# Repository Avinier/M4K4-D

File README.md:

# Makad / M4K4-D

> **Current project overview**: last reconciled **12 November 2026**
>
> Foundation approved: **14 August 2026** · V1 deadline: **5 December 2026**

**Makad**, technical designation **M4K4-D** and commonly shortened to **M4**, is a personal droid. M4 is intended to occupy the kind of companion role R2-D2 occupied for Luke Skywalker: recognizable, attentive, expressive, and full of character.

The central V1 priority is simple:

> **M4 should feel alive.**

Makad's defining advantage is expressiveness. That expression comes from what M4 understands, sees, and hears, and from how convincingly its display, status light, astromech audio, head, wheeled base, and timing communicate one intent.

## Authority

- [`project/00-foundation`](project/00-foundation/) is the product-intent authority.
- [`project/03-build`](project/03-build/README.md) governs every engineering decision, part selection, BOM change and CAD edit from 2026-09-28. Its ledger is [`decisions.md`](project/03-build/decisions.md) and its parts register is [`BOM.csv`](project/03-build/BOM.csv).
- [`project/01-system`](project/01-system/) and [`project/02-prototypes`](project/02-prototypes/) are read-only engineering reference. Where they disagree with `03-build`, `03-build` wins.

[`MEMORY.md`](MEMORY.md) is a short chronological log of the project's turning points.

## Current design

M4 is a battery-powered floor droid with a three-axis head, an animated face, a camera-side status light, body-mounted hearing and speech, and a two-wheel base. The head carries the display, camera, status light and C2 motion controller. The body carries the yaw stage, four I²S microphones, the speaker, main compute and the bought power modules; the chassis carries the battery, drive and floor sensors. Floor mode is primary; tabletop mode inhibits locomotion by default.

Drive geometry is Ø84 mm wheels on a ~170 mm track with a front ball caster and a mandatory rear anti-tip keel ([dimensional baseline](project/01-system/dimensional-baseline.md) v1.15). The whole robot is modelled in [`project/03-build/final/v1`](project/03-build/final/v1/README.md); subsystem CAD lives in [01-chassis](project/03-build/01-chassis/), [02-body](project/03-build/02-body/) and [03-head](project/03-build/03-head/).

### Selected components

States follow the [BOM](project/03-build/BOM.csv): selected parts are settled but not yet measured or bench-proven.

| Item | Selection | Record |
|---|---|---|
| Face display | Waveshare ESP32-S3-LCD-4.3, **no-touch, SKU 30493**: 800×480 IPS with on-board ESP32-S3/LVGL renderer | [display study](project/01-system/display-candidate-study.md) |
| Head camera | Raspberry Pi Camera Module 3 **Wide**, **SC0874**; ribbon crosses pitch and roll in a free loop behind the head | [D-105](project/03-build/decisions.md#d-105) |
| Main compute (C0) | **Raspberry Pi 5, 2 GB** with the official Active Cooler, on PCB-09 (2 × RS-422 link adapter) | [D-048](project/03-build/decisions.md#d-048), [04-pcbs](project/03-build/04-pcbs/README.md) |
| Head motion controller (C2) | Waveshare **ESP32-S3-Zero** on the custom PCB-12 carrier | [D-102](project/03-build/decisions.md#d-102) |
| Base controller (C3) | Espressif **ESP32-S3-DevKitC-1 v1.1** on the custom PCB-10 carrier | [04-pcbs](project/03-build/04-pcbs/README.md) |
| Head actuators | Yaw: **Waveshare ST3215-HS** at 11.1 V. Pitch and roll: **Feetech STS3045M** at 6.3 V. Candidates until bench tests B1–B6 | [D-046](project/03-build/decisions.md#d-046)–[D-049](project/03-build/decisions.md#d-049) |
| Drive | **ThinkRobotics MOT3001-6V230RPM** encoder gearmotors (received), two DRV8833 carriers, printed PETG/TPU wheels, Pololu #2691 ball caster | [D-003](project/03-build/decisions.md#d-003) |
| Battery | **2S1P Samsung INR18650-25R** (7.2 V, 18 Wh) with a bought TIFPS0629 protection board and copper ballast; charged off-board (ISDT PD60) | [D-093](project/03-build/decisions.md#d-093) |
| Power | Pololu #2813 pushbutton switch, two S18V20ALV servo rails, two S13V30F5 5 V rails, INA226 monitor | [D-094](project/03-build/decisions.md#d-094), [module selection](project/03-build/module-selection.md) |
| Audio and IMU | Visaton K 50 WP speaker, MAX98357A amp, 4 × INMP441 mics, Adafruit LSM6DSOX base IMU | [D-094](project/03-build/decisions.md#d-094) |
| Control split | C0 owns semantic behaviour; D1 renders eyes; C2 owns head trajectory and local safety; C3 owns base loops and local hazards. Links are differential UART; C2 relays face/light state locally | [control topology](project/01-system/control-topology-options.md) |

## Current build state

The design is ahead of the physical robot. The whole-robot CAD is integrated and checked; first parts have arrived; nothing is printed, wired or running.

| Area | State (2026-11-12) |
|---|---|
| CAD | Chassis, body and head v1 are integrated in `final/v1` with targeted checks. Tipping margin a_tip 1.670 neutral / 1.646 worst pose against 1.582 ([D-095](project/03-build/decisions.md#d-095)); camera-loop ballast keeps the worst-yaw margin above 1.5% ([D-105](project/03-build/decisions.md#d-105)). Not yet a fabrication release for body and head. |
| Electrical | D-093 replaced the custom power boards with bought modules. The [harness](project/03-build/05-harness/README.md) topology is drawn but on **electrical HOLD** ([D-096](project/03-build/decisions.md#d-096)). Custom boards: PCB-09 rev B routed; PCB-10/11/15 rev A; PCB-08/12/14/16 rev A drafts, not ordered. |
| Procurement | Modules and small parts ordered 2026-11-08; deliveries logged in [BOM-deliveries.md](project/03-build/BOM-deliveries.md). Open actions in [TODO.md](project/03-build/TODO.md). |
| Printing | Chassis print package exported to [04-print](project/04-print/README.md); body and head prints not started. |
| Software / firmware | [Firmware requirements](project/03-build/04-software/firmware-requirements.md) recorded; timebase, link contract and behaviour are specified more than implemented. |
| Physical tests | None run. Bench register N1–N12 and actuator tests B1–B6 are open. |

`visuals/` are provisional references; several show superseded details (mouths, ear microphones, yoke-mounted ears).

## Immediate next work

- **Receive and measure** the ordered parts; record them in the BOM and correct dependent CAD.
- **Run the bench tests**: power switch, servo and 5 V rails (N1–N12), Feetech actuators (B1–B6), pack protection acceptance.
- **Clear the harness HOLD** from measured peaks, then build and test the harness.
- **Finish the custom boards** (PCB-08, 12, 14, 16) and order all of them together.
- **Print and assemble the chassis**, then body and head, through [04-print](project/04-print/README.md).
- **Implement firmware and software** on the same timeline: C2/C3, C0 behaviour and perception, the serial link and face rendering.

## Documents

### Product intent: authoritative

- [Vision](project/00-foundation/vision.md)
- [V1 scope](project/00-foundation/v1-scope.md)
- [Constraints](project/00-foundation/constraints.md)
- [Success criteria](project/00-foundation/success-criteria.md)
- [Core interaction scenarios](project/00-foundation/core-interaction-scenarios.md)

### Build: governing

- [03-build overview](project/03-build/README.md): status, file map and build rules
- [Decisions ledger](project/03-build/decisions.md), [BOM](project/03-build/BOM.csv), [simplification plan](project/03-build/simplification-plan.md)
- [Whole robot (final v1)](project/03-build/final/v1/README.md) and its [print guide](project/03-build/final/v1/printguide.md)
- [Custom PCBs](project/03-build/04-pcbs/README.md), [harness](project/03-build/05-harness/README.md)
- [Printing](project/04-print/README.md)

### Engineering reference (read-only)

- [Dimensional and packaging baseline](project/01-system/dimensional-baseline.md)
- Ledgers: [mass/envelope](project/01-system/mass-envelope-ledger.md), [power/energy/thermal](project/01-system/power-energy-ledger.md), [candidate sourcing](project/01-system/candidate-sourcing-matrix.md)
- Studies: [control topology](project/01-system/control-topology-options.md), [display](project/01-system/display-candidate-study.md), [camera](project/01-system/camera-candidate-study.md), [head harness](project/01-system/head-harness-routing-study.md), [timebase](project/01-system/timebase.md)
- [System design brief](project/01-system/system-design-brief.md), [risk-prototype plan](project/01-system/risk-prototype-plan.md), [workbench](project/01-system/workbench.md), [run-record convention](project/01-system/run-record-convention.md)
- Risk prototypes: [head](project/02-prototypes/RP-01-head/), [electrical](project/02-prototypes/RP-02-electrical/README.md), [locomotion](project/02-prototypes/RP-03-locomotion/README.md), [coordination](project/02-prototypes/RP-04-coordination/README.md), [interaction](project/02-prototypes/RP-05-interaction/README.md), [CAD layouts](project/02-prototypes/RP-06-cad/README.md), [following](project/02-prototypes/RP-07-following/README.md)
- Earlier memory logs: [`archive/`](archive/)

## Repository

```
project/00-foundation/   product intent and constraints      authoritative
project/01-system/       system studies and ledgers          reference
project/02-prototypes/   risk prototypes and early CAD       reference
project/03-build/        decisions, BOM, CAD, PCBs, harness  governs
project/04-print/        print lab, workflow, STL exports
visuals/                 provisional renders
archive/                 earlier memory logs
MEMORY.md                chronological log of turning points
README.md                this orientation
```

## Identity and design direction

M4 is a droid, not a desktop assistant, smart speaker, or generic social robot. The approved direction is:

- strongly inspired by Star Wars droids;
- cyberpunk, rugged, scrappy, and characterful;
- mechanical rather than glossy or appliance-like;
- modular and screw-together, with visible fasteners, panels, seams, and service access as part of the personality;
- eyes only on the face, no mouth;
- approachable without optimizing for minimum size;
- open to substantial redesign from the current renders.

## V1 Core

V1 is not complete unless the following outcomes work together as one droid. Exact wording lives in [`v1-scope.md`](project/00-foundation/v1-scope.md) (SCOPE-01…21).

**Expression and character** — animated face on the onboard display; powered roll, pitch and yaw head motion; at least one controllable LED beside the camera; a builder-authored non-English astromech language; idle aliveness without manual control; display, LED, audio, head, base and timing express one intent; at least one bounded excited spin.

**Understanding and perception** — natural spoken interaction within the approved scenarios; invocation forms **"M4," "M4K4," and "Makad"**; visual acquisition of a nearby person or face; tracking maintained or reacquired through later-defined test cases.

**Mobility and following** — battery-powered wheeled floor droid; "come here" finds, approaches and stops at a bounded distance; "follow me" tracks the selected person through an approved indoor route; obstacles, stopping, target loss and unsafe conditions are handled without continuing blindly.

**Utility and entertainment** — display the time; create and signal timers and alarms; start Spotify playback through an approved integration; eyes "vibe" to music.

**Operation and construction** — untethered on onboard battery for at least 20 minutes; floor mode primary; tabletop mode inhibits locomotion by default and protects edges; accessible stop or cutoff with bounded failure; assembled, started, demonstrated, inspected and serviced from documentation.

**Candidate:** spatial/directional hearing, included only if it materially improves an approved interaction. Everything else is uncommitted; there is no permanent "never" list.

## Approved Core scenarios

Source: [`core-interaction-scenarios.md`](project/00-foundation/core-interaction-scenarios.md).

**1. Wake, socialize, assist.** M4 idles head-down. A person calls its name. M4 wakes as one coordinated performance: three-axis head rise, eyes, camera-side LED, astromech acknowledgement, face acquisition and gaze. A greeting produces an in-character response. The person can request the time, a timer, an alarm, or Spotify playback; M4 confirms visibly, performs it, and vibes during music.

**2. Come here and follow me.** On an approved floor, the person invokes M4 and says "come here." M4 acknowledges, searches, acquires, turns, approaches safely and stops approximately 0.6–0.9 m away. "Follow me" makes M4 follow through an approved route of up to about 3 m at no more than about 0.5 m/s while handling obstacles and target loss. When continuing is unsafe, M4 stops and says so. M4 performs an excited spin and settles.

## Success definition

V1 succeeds when M4 delivers these interactions as a convincing, repeatable droid encounter on battery power, not as a sequence of manually rescued subsystem demos. The validation categories and open thresholds are in [`success-criteria.md`](project/00-foundation/success-criteria.md) (SC-01…25).

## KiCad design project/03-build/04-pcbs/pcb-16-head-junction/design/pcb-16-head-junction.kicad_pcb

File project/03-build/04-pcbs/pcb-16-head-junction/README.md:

# PCB-16 — Head junction

Passive FFC-to-wire break for the two head FFCs (W42 power, W43 signal). It lies flat on the yaw disc beside the +Y yoke leg's foot, so the tilting head needs only wires across its pitch and roll joints ([D-103](../../decisions.md#d-103)).

| | |
|---|---|
| Register | [04-pcbs board register](../README.md#board-register) |
| Project BOM | CH-111 in [BOM.csv](../../BOM.csv) |
| Location | Head, yaw frame: flat on the yaw disc (M012) top, over the channel's outer end |
| Specification | [D-103](../../decisions.md#d-103), [D-100](../../decisions.md#d-100), [D-101](../../decisions.md#d-101), [D-102](../../decisions.md#d-102) |
| Final CAD | `Custom PCBs › PCB-16 head junction` (installed by `pcb_integration.py`); fixings and reserves `PCB16`, `PCB16_RESERVES` in [makad-v1.step.py](../../final/v1/cad/makad-v1.step.py) |

## Stages

See [workflow.md](../workflow.md) for what each stage involves and when it is done.

| Stage | Status | Revision / evidence | Date |
|---|---|---|---|
| 1. Design | **Rev A draft complete**; [fab/revA](fab/revA/README.md) written (**do not order**) | [design/](design/): Nightly ERC 0/0, netlist audit 10/10 on 44 pins, parity DRC 0/0/0; [STEP](cad/pcb-16-head-junction-revA.step); [fit](../../final/v1/cad/check_pcb16_fit.py) 7/7 | 2026-11-10 |
| 2. Procure | Waits for the gates in [fab/revA](fab/revA/README.md#before-ordering) (D-064 batch) | — | — |
| 3. Integrate | Rev A STEP installed in the final CAD with disc inserts and screws; `check_pcb_integration.py` PASS (10 boards) | Physical acceptance open | 2026-11-10 |

## Inputs

**Why a board on the disc.** D-052 meant the head FFCs to climb the +Y leg into the pitch frame. The pitch servo fills the inside of that leg from Z ≈ 15 to 65 (head-local), so that route is blocked. A roll × pitch sweep shows the band from the disc top (Z −34.5) to about Z −24 stays clear beside the leg foot. The head already reserves everything below Z −30.5 as moving-part clearance (`SWEEP_FLOOR_Z`), and PCB-16 with both FFC arrivals stays under it.

**Envelope (head-local).**
- Board: X −62.4…−26, Y 35.5…54, Z −34.5…−33.7.
- The edge steps in to X −47.6 from Y 47.7, keeping 0.3 mm from the leg foot's flare (which reaches X −47.95 from Y 48.05 at the disc).
- The −X tab (Y 35.5…41) clears the foot's M2 screw heads, which start at Y 46.97.
- Two M2 holes at (X −57.4, Y 38.2) and (X −31.9, Y 52.0) take M2 × 4 button screws into M2 inserts in the 4 mm disc plate, leaving a 0.8 mm floor.

**FFC arrival** (`HARNESS_HEAD_FFC_*` in the droid CAD, at PCB-14's D-101 planes):
- The head FFCs rise up the bore (Y ±4.65), lie flat in the disc channel, and leave it from Y 30.
- The **lower** FFC (**W43 signal**) S-bends up (about R3, `E`) and runs 1 mm straight into **J1** (mouth Y 36.0).
- The **upper** FFC (**W42 power**) rises higher, runs 0.055 mm over J1's closed body and drops into **J2** (mouth Y 43.4).
- The **CSI** is the top FFC and leaves before Y 29.8 (`HARNESS_HEAD_CSI_EXIT_UNROUTED`). Its path to the camera is open.
- Cassette input: W43 on PCB-14 board 3, W42 on board 2, CSI on board 1. Confirm with the fold mock-up.
- **Plug order:** W43 into J1 first, close J1, then W42 over it into J2.

**Conductor 1.** The head FFC carries conductor 1 on its −X edge (D-101), and each ZIF's contact 22 is at −X. So **contact *m* carries conductor 23 − *m***, and nets are named by conductor (PCB-08's `J8-6`/`J8-7` maps).

## Circuit and pads

[Schematic](design/pcb-16-head-junction.kicad_sch) ([PDF](design/pcb-16-head-junction-schematic.pdf)), written by [build_schematic.py](design/build_schematic.py). The board is passive and the four grounds stay separate; PCB-12 bonds them (D-100). Wire pads ([generate_wire_pads.py](../lib/generate_wire_pads.py)) sit where their nets are, are bare copper, and are left out of the BOM and position files.

| Ref | Part | Nets / wires |
|---|---|---|
| J1 | FH34SRJ-22S, near | W43: conductors 1/4/7/9 `GND_SIG`, 2 C0TX+, 3 C0TX−, 5 C2TX−, 6 C2TX+, 8 `SERVO_DATA`; 10–22 isolated |
| J2 | FH34SRJ-22S, far | W42: 1–7 `+6V3_HEAD_PR`, 8–14 `GND_HEAD`, 15–16 `+5V_C2`, 17–18 `GND_C2`, 19–20 `+5V_DISPLAY`, 21–22 `GND_DISPLAY` |
| J3 | 2 pads 2.2 × 3.5 mm | 1 `+6V3_HEAD_PR`, 2 `GND_HEAD`: AWG20 servo bundle to the pitch servo's 5264 (daisy chain to roll). Pad 2 also takes PCB-12's J2-lead `GND_HEAD` wire |
| J4 | 7 pads 1.0 × 2.5 mm | 1 `GND_SIG`, 2 C0TX+, 3 C0TX−, 4 C2TX−, 5 C2TX+ (PCB-12 J1-lead wires 1–5); 6 `SERVO_DATA` (PCB-12 J2-lead wire 2); 7 `SERVO_DATA` (servo bundle) |
| J5 | 2 pads | 1 `+5V_C2`, 2 `GND_C2` (PCB-12 J1-lead wires 6–7) |
| J6 | 2 pads | 1 `+5V_DISPLAY`, 2 `GND_DISPLAY` (to D1) |

The PCB-12 leads are pre-crimped single-ended GH7 and GH2 leads, cut and soldered here; they plug into PCB-12 J1/J2. The head comes off by unplugging at PCB-12, the servo and D1.

**Checks.** ERC 0/0 ([report](design/schematic-erc.rpt)). [audit_netlist.py](design/audit_netlist.py) **10/10** ([netlist-audit.json](design/netlist-audit.json)): W42 and W43 conductor maps against `J8-6`/`J8-7`, no power on W43, the pad maps, the grounds kept separate, the `SERVO_DATA` hub.

## Layout

[layout_pcb16.py](design/layout_pcb16.py) writes the board headless (PCB-12's method). Mapping: KiCad x = X + 142.4, y = 150 − Y, component face +Z.
- **Board:** two layers, 0.8 mm.
- **J2 power** runs straight back into its pads: `+6V3_HEAD_PR` and `GND_HEAD` as F.Cu fields over seven contacts each (2.4 A), the C2 and display pairs as 0.3 mm tracks.
- **J1 signal:** its four `GND_SIG` contacts join under the ZIF body (Hirose allows traces there). The signal lanes leave the pad tails, cross the band between the ZIFs and land on the J4 column.
- **DRC:** Nightly parity **0/0/0** ([report](design/placement-drc.json)). A scratch copy with a 0.5 mm edge rule flags the four ZIF tabs.
- **STEP:** [cad/pcb-16-head-junction-revA.step](cad/pcb-16-head-junction-revA.step), with the detailed FH34SRJ model.

**Fit ([`check_pcb16_fit.py`](../../final/v1/cad/check_pcb16_fit.py), 7/7).**
- Placed; clear of the yaw-frame parts (leg foot 0.3 mm).
- Under the sweep floor; 10.04 mm from the moving head over 30 poses.
- FFC paths into both mouths; inserts in the plate; conductor 1 on contact 22.

**Mass:** about 1.34 g (`check_batch_mass.py`).

## Open

- ~~The wire bundle's routes across the pitch and roll joints~~: routed by [D-104](../../decisions.md#d-104) from the +X exit, along the disc to the −Y leg and through a hollow −Y trunnion (`check_d104_head_routes.py` 7/7). The +Y exit reserve stays unused.
- ~~The CSI's path to the camera across both joints~~: [D-105](../../decisions.md#d-105) folds it out at the CSI exit onto the disc to a bracket behind the head and a free loop to the rear cover (`check_d105_csi_loop.py` 10/10).
- A strip of the received FFC to confirm the S-bends.
- Pad sizes against the received wire.

## Log

- **2026-11-10:** rev A draft ([D-103](../../decisions.md#d-103)): yaw-disc FFC-to-wire break, stepped FH34SRJ pair, per-net wire pads. The board moved 5.5 mm toward −Y and stepped past the leg foot after the fit check found it on the foot; ERC 0/0, netlist audit 10/10, parity DRC 0/0/0, fit 7/7; installed in the final CAD (integration PASS, 10 boards).

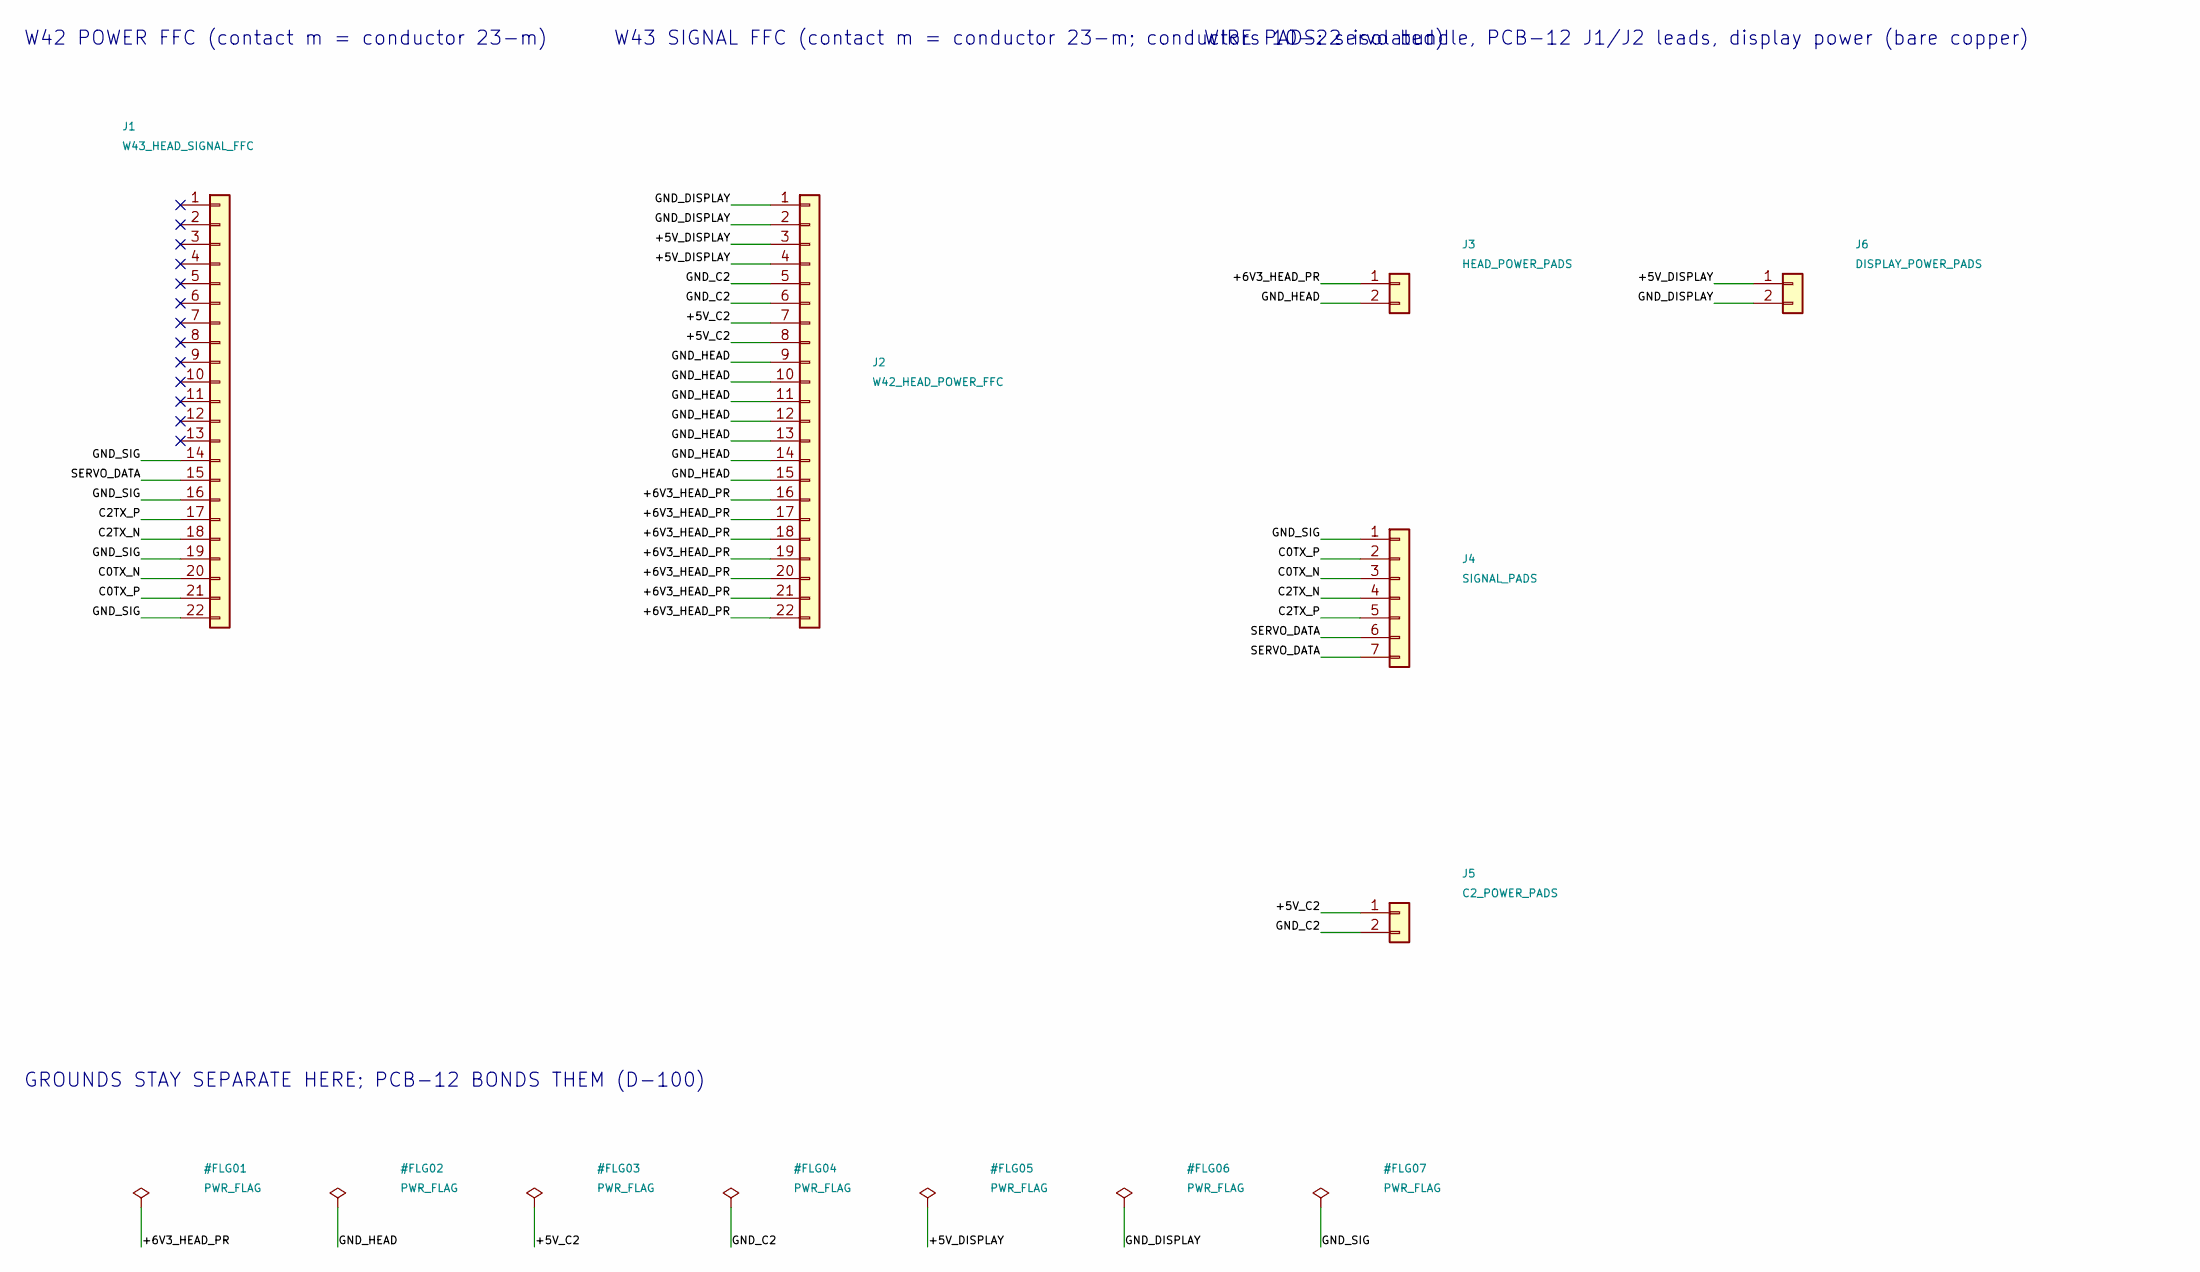
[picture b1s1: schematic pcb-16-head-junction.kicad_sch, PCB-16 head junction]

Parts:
J1: W43_HEAD_SIGNAL_FFC; Hirose_FH34SRJ-22S-0.5SH_1x22_P0.50mm
J2: W42_HEAD_POWER_FFC; Hirose_FH34SRJ-22S-0.5SH_1x22_P0.50mm
J3: HEAD_POWER_PADS; WirePads_Power_1x02_P3.5mm
J4: SIGNAL_PADS; WirePads_1x07_P1.5mm
J5: C2_POWER_PADS; WirePads_1x02_P1.5mm
J6: DISPLAY_POWER_PADS; WirePads_1x02_P1.5mm

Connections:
/+5V_C2: J2.7, J2.8, J5.1
/+5V_DISPLAY: J2.3, J2.4, J6.1
/+6V3_HEAD_PR: J2.16, J2.17, J2.18, J2.19, J2.20, J2.21, J2.22, J3.1
/C0TX_N: J1.20, J4.3
/C0TX_P: J1.21, J4.2
/C2TX_N: J1.18, J4.4
/C2TX_P: J1.17, J4.5
/GND_C2: J2.5, J2.6, J5.2
/GND_DISPLAY: J2.1, J2.2, J6.2
/GND_HEAD: J2.9, J2.10, J2.11, J2.12, J2.13, J2.14, J2.15, J3.2
/GND_SIG: J1.14, J1.16, J1.19, J1.22, J4.1
/SERVO_DATA: J1.15, J4.6, J4.7

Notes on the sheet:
W42 POWER FFC (contact m = conductor 23-m)
W43 SIGNAL FFC (contact m = conductor 23-m; conductors 10-22 isolated)
WIRE PADS: servo bundle, PCB-12 J1/J2 leads, display power (bare copper)
GROUNDS STAY SEPARATE HERE; PCB-12 BONDS THEM (D-100)

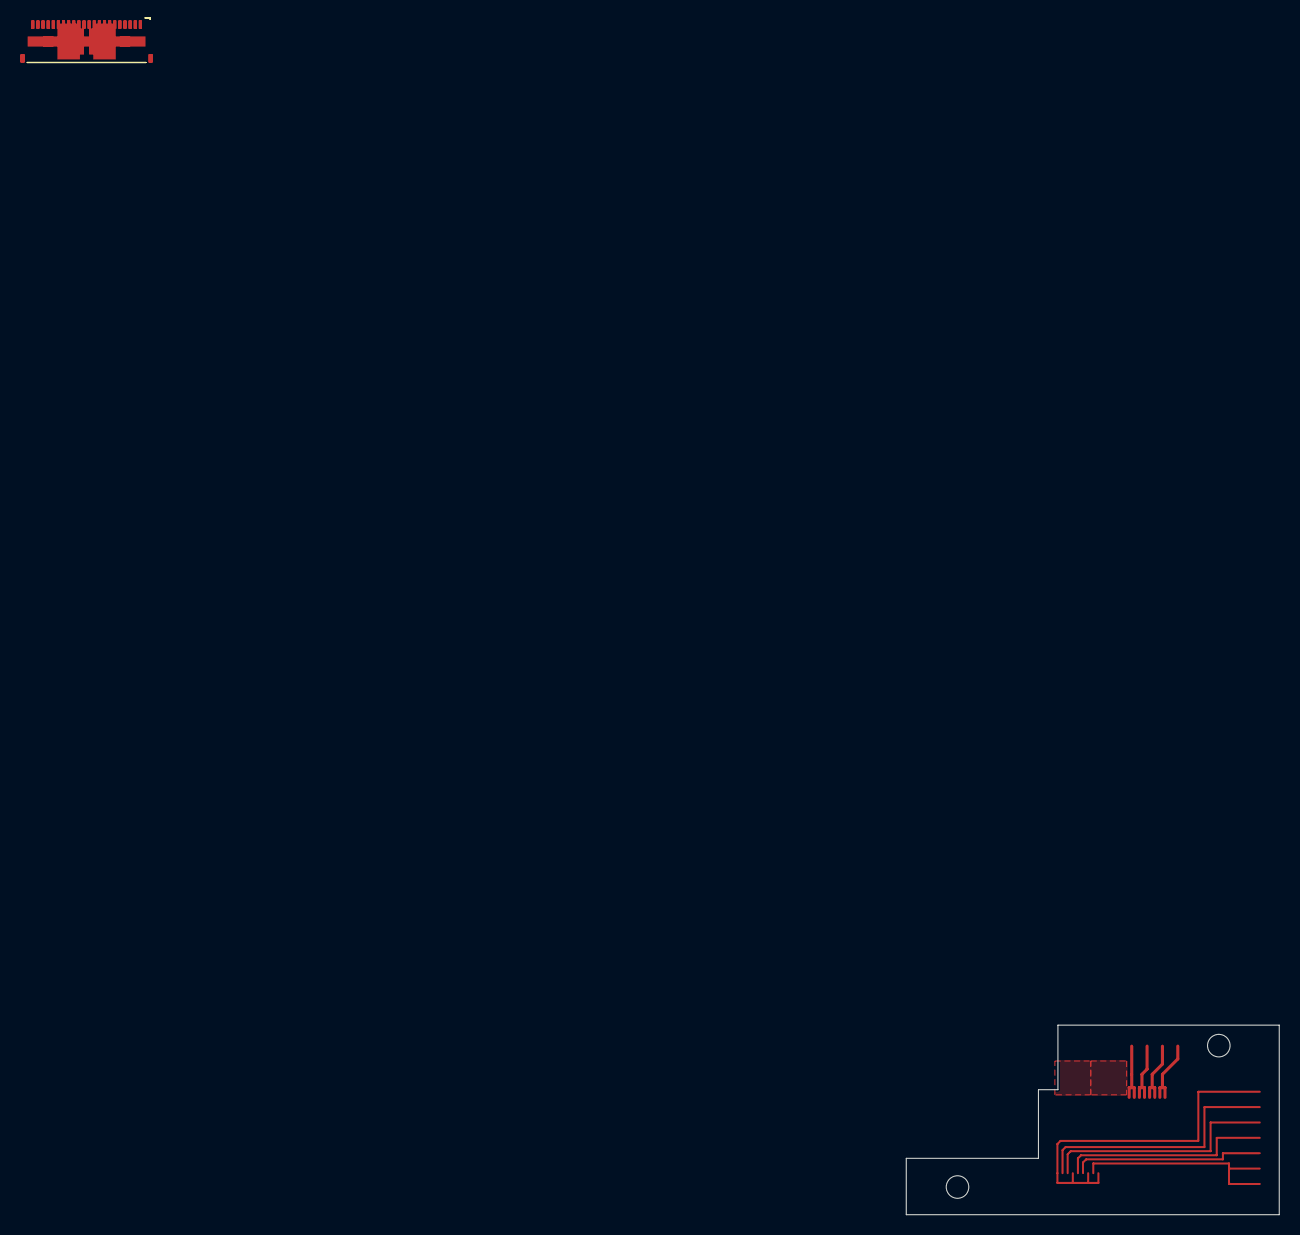
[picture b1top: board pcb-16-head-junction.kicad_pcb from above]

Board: 2 copper layers, 36.4 x 18.5 mm, 6 parts (0 on the bottom side), 12 nets.

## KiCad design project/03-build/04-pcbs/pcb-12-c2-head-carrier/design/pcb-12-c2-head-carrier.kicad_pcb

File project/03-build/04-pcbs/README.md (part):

# 04 — PCBs

This folder holds the schematic, layout, fabrication and electrical-validation work for the robot's custom boards. It is a work area, not a fabrication release. Part records stay in the [project BOM](../BOM.csv); every selection and change goes in the [build decisions](../decisions.md). It replaces the former `04-custom-pcb/` folder ([D-038](../decisions.md#d-038)).

Each custom board is designed, procured and integrated into the final CAD one at a time, in its own `pcb-NN-name/` folder. [workflow.md](workflow.md) describes the three stages and tracks each board's progress.

## Tools

Chosen in [D-058](../decisions.md#d-058); layout tool and routing changed by [D-060](../decisions.md#d-060).

| Tool | Used for | Where |
|---|---|---|
| KiCad 10.99 (nightly) + KiPy | Schematic and layout, driven through KiPy and computer-use tools; the GUI for review | `/Applications/KiCad-nightly` (build 20261024, `de08734017`), side by side with 10.0.6 in `/Applications/KiCad`. KiPy (`kicad-python` 0.8.0) in `~/.local/share/kipy/venv`; it talks to the running GUI, and the nightly has no bundled `pcbnew` Python. Each board's project is in its folder's `design/` |
| `kicad-cli` (same install as the layout) | ERC, DRC with the schematic-to-board check, Gerbers, drill, pick-and-place, BOM, board STEP, renders | `/Applications/KiCad-nightly/KiCad.app/Contents/MacOS/kicad-cli` (10.99). The 10.0.6 CLI in `/Applications/KiCad` may not read files the nightly saved |
| [`tools/kp.py`](tools/kp.py) | KiPy layout helpers: place (restores 3D models after a flip), octolinear tracks, vias, audit, DRC. Steps in [design-playbook.md](design-playbook.md) | Run with `~/.local/share/kipy/venv/bin/python` against the open PCB editor |
| JLCPCB (default), PCBWay, Lion Circuits (MII service) | PCB fabrication and assembly (PCBA). These three only. Layouts follow the [fab-neutral rules](#fab-neutral-design-rules), and the fab is chosen by quote ([D-062](../decisions.md#d-062)) | — |
| text-to-cad (cadgen) | Stage 3: the board STEP placed in the robot CAD | Project runtime 0.4.28 (see [final/v1](../final/v1/README.md)) |

## Layout rules

These rules take priority over D-058 ([D-060](../decisions.md#d-060); builder, 2026-10-14). They come from someone else's experience of LLM-driven KiCad layout. When an LLM lays out a board, it must:

1. use KiCad 10.99 (the nightly build, which adds scripting features) and drive it through KiPy and computer-use tools;
2. not use an autorouter such as Freerouting;
3. place components one at a time or in small functional groups;
4. adjust placement after routing where that helps;
5. route with octolinear traces, organised into buses of parallel, equally spaced tracks. Plan fanouts first. Keep detours and roundabout routes to a minimum, especially on signal nets. Size track widths and pours for each net's current. Optionally, write reusable scripts that check these properties and use them to check the work.

## Fab-neutral design rules

Only three fabs make Makad boards: **JLCPCB** (China, the default), **PCBWay** (China) and **Lion Circuits** (Bengaluru), on its **MII** (Make in India) service ([D-062](../decisions.md#d-062), builder, 2026-10-25). Every board is laid out so that any of the three can make it on its standard service, with no layout change. The rule set is the strictest standard 2-layer, 1 oz limit of the three. Each board carries it as a KiCad custom rules file, `design/<board>.kicad_dru`, copied from [PCB-15's](pcb-15-nose-hall/design/pcb-15-nose-hall.kicad_dru). The fab is chosen by quote at procure.

| Rule | Fab-neutral minimum | JLCPCB | PCBWay | Lion Circuits MII |
|---|---|---|---|---|
| Track width and copper gap | **0.16 mm** | 0.10 | 0.10 | 0.152 (6 mil) |
| Via | **0.35 mm hole, 0.67 mm pad** (ring 0.16) | hole 0.15, pad 0.25 | hole 0.15, ring 0.15 | drill 0.35, ring 0.152 |
| Via to other copper | **0.31 mm**, from the via's copper and from its hole | — | — | 12 mil (0.305), via to trace |
| Hole to hole | **0.31 mm** | — | — | 12 mil between vias |
| Copper to routed edge | **0.3 mm** | 0.2 | 0.25 | 0.3 |
| Solder-mask web between pads | **0.16 mm** | 0.10 | not stated; confirm | 0.152 |
| Silkscreen text | **1.0 mm high, 0.16 mm line**, or leave silkscreen off | 1.0 | 0.8 | 0.58, line 0.152 |
| Board thickness tolerance | **State it on the order** when the mounting needs it | ±10 % | ±10 % at 1.0 mm and thicker; confirm below | ±10 % |
| Assembly, minimum board | **Panelise** small boards | 10 × 10 mm | quote; 0402 parts get an engineering review | 50 × 100 mm |

Lion's page lists three services. **MII** is the target. **Custom** is looser (0.25 mm drill, 10 mil via spacing), so an MII layout also suits it. **Rush** is tighter (0.4 mm drill, 8 mil tracks, 14 mil via spacing) and is not a target. A board that needs Rush is checked against it first.

Sources, read 2026-10-25: [JLCPCB](https://jlcpcb.com/capabilities/pcb-capabilities), [PCBWay](https://www.pcbway.com/capabilities.html), [Lion Circuits](https://lioncircuits.com/pcb-manufacturing-capabilities). Read the pages again before each order. If a fab tightens a limit, tighten the rule here first.

## Board register

**[D-093](../decisions.md#d-093) (2026-11-06):** PCB-02, 03, 04, 05, 06 and 07 are replaced by bought modules and PCB-13 is deleted. The custom boards are PCB-08, 09, 10, 11, 12, 14 and 15. The superseded rows are kept as the record. The change map is in [simplification-plan.md](../simplification-plan.md).

| ID | Board | Location | BOM | Status | Work still required |
|---|---|---|---|---|---|
| PCB-01 | 2S pack protection | Chassis tub, on the pack | CH-023 | **Bought:** Robocraze TIFPS0629 ([D-019](../decisions.md#d-019)); the RP-02 custom design is reference only | Bench acceptance before cells: [power-boards.md §3](power-boards.md#3-pcb-01--tifps0629-acceptance-before-cells-are-connected) |
| PCB-02 | Charger (BQ25798), on/off latch, pack sense, `ENERGY_OK` | Body, behind the rear panel (vertical) | CH-041 | **Superseded by [D-093](../decisions.md#d-093): bought.** A pushbutton power switch module and an INA226/219 voltage/current monitor; no charger (the pack is charged outside the robot). Rev A routing archived in the [board folder](pcb-02-charger/README.md) | Module selection and India stock ([plan level 3](../simplification-plan.md#7-levels-of-work)) |
| PCB-03 | Motor gate, permit chain, head 5 V rail, drive feeds | Body, above the tub | CH-042 | **Superseded by [D-093](../decisions.md#d-093): bought.** Two buck-boost modules: head pitch/roll 5.5 V and yaw 11.1 V. Drive feeds come straight from the switched bus with the SMBJ8.5A and bulk at each `VM`; the yaw servo plug moves to PCB-08 | Module selection and India stock |
| PCB-04 | Five branch converters (C2, base, Pi, display, audio) | Body, under the compute tray | CH-043 | **Superseded by [D-093](../decisions.md#d-093): bought.** Two Pololu S13V30F5 5 V buck-boost modules ([D-094](../decisions.md#d-094)): one for the Pi, one shared by C3, amp, C2 and display | Module selection and India stock; series Schottky in `W11` (C3 USB back-feed) |
| PCB-05 | Audio front end (MAX98357A, 2 × ADAU7002) | Body, above the Pi, hung from the frame on three M2 SMT spacers ([D-067](../decisions.md#d-067)) | BO-002 | **Superseded by [D-093](../decisions.md#d-093): bought.** MAX98357A breakout (BO-007, promoted from bench) and an audio hub. Rev A archived in the [board folder](pcb-05-audio-front-end/README.md) | Amp mount in CAD; four-mic I²S overlay on the bench |
| PCB-06 ×4 | PDM microphone board | Body shell bosses | BO-005 | **Superseded by [D-093](../decisions.md#d-093): bought.** Four I²S mic breakouts with an L/R pin (INMP441 class), two per lane on SDI0/SDI1. Rev A archived in the [board folder](pcb-06-pdm-mic/README.md) | Boss redesign for the breakout outline; overlay bench test before the shell is printed |
| PCB-07 | Base IMU (ICM-42688-P) | Chassis | CH-021 | **Superseded by [D-093](../decisions.md#d-093): bought.** SPI 6-axis IMU breakout on the existing `J10-7` pinout, on a printed adapter on the J15A holes | Breakout selection; adapter in CAD |
| PCB-08 | Yaw junction (clock-spring stationary end) | Body, under the yaw adapter plate | CH-083 | **Rev A draft (do not order)** ([D-100](../decisions.md#d-100)). **Rescoped by [D-093](../decisions.md#d-093):** drops the `W23a`/`W23b` permit and status sideband and `ARM_REQ`; gains the yaw servo plug (`+11V1_YAW`, GND, `SERVO_DATA`, was PCB-03 `J3-5`). Spec; grows +X to X 20 for two 22-pin 0.5 mm ZIFs, `J8-6` power and `J8-7` sideband, taking the cassette FFCs ([D-044](../decisions.md#d-044)) | **Rev A layout routed** ([D-100](../decisions.md#d-100) amendment): Nightly parity DRC 0/0/0 with head copper fields; 6.3 V head on 7 + 7, `J8-7` signal-only with `GND_SIG`; stepped FH34SRJ pair. Fold mock-up, head-riser tail conflict, N2(b) and populated fit open. Body-side pinout and mating rule: [05-harness](../05-harness/README.md) (D-039) |
| PCB-14 | Yaw rotor joiner boards ([D-052](../decisions.md#d-052); replaces the D-044 Ø35 ring): three identical vertical 0.8 mm boards (a fourth identical board joins the CSI on the [D-105](../decisions.md#d-105) camera-loop bracket), each a straight-through 22-pin 0.5 mm FFC joiner ([D-101](../decisions.md#d-101): lower contact *n* → upper 23 − *n*) with a down-facing FH34SRJ for its cassette FFC (`W37`/`W42`/`W43`) and an up-facing one for the head FFC, both on the +Y face; 4.5 mm pitch (D-101); tabs seat in the rotor posts | Body, inside the rotating yaw hub (Z 133.9–150.7) | BO-062 (×3) | Rev A draft (do not order) | FH34SRJ sample: open-actuator height (`E` 3.4 mm); fold mock-up at the 4.5 mm planes; standard-mini CSI end in FH34SRJ and the BO-050 CSI test; CSI Pi-end conductor 1 when the drop is drawn; stage-3 board replacement |
| PCB-09 | C0 link adapter (2 × RS-422, audio pass-through, enclosure-fan switch `J9-4`) | Body, on the Pi header, on two M2.5 × 11 standoffs at Pi holes 3/4 | CH-084 | **Rev B routed and CAD fitted on `pcb-09-revB`; not released** ([D-092](../decisions.md#d-092), [D-098 amendment](../decisions.md#d-098)): Samtec SSW-120-01-T-D socket, 4 layers, retained rev A functions and connector pinouts, plus J6 six-net button/OFF/INA226 `i2c-gpio` service interface; [board folder](pcb-09-c0-link-adapter/README.md). Final CAD uses the rev B STEP | Nightly DRC 0/0/0, fit 8/8, mount 7/7 and final integration PASS. `fab/revB` is a draft; wait for #2813, Pi-image and populated bench acceptance before the D-064 order. CR-02 boot/overlay and fan current, socket seating, contact check and harness pull test remain |
| PCB-10 | C3 controller carrier (watchdog, READY, sleep gate, Hall and TCRT circuits) | Body, −Y side wall | CH-044 | **Inputs frozen** ([D-068](../decisions.md#d-068), [board folder](pcb-10-c3-carrier/README.md)): two screws and two printed edge hooks, Espressif DevKitC-1 v1.1 only, TPS3436CCCBG from Mouser India, GPIO map v0.2, `J10-2` named by direction ; [KiCad geometry installed in final CAD](../final/v1/README.md#pcb-geometry-in-the-whole-robot-assembly) | **Design done, rev A** (four layers; DRC clean; `check_pcb10_fit.py` 7/7; [fab outputs](pcb-10-c3-carrier/fab/revA/README.md)); GPIO map v0.3, `J10-2` in U2's order; U2/U3 from Mouser India, consigned; nose, TCRT and head-riser harness re-routes at stage 3; [D-093](../decisions.md#d-093): `J10-12` is unused (PCB-03 is gone) and `W11` gets a series Schottky against USB back-feed; no re-spin |
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
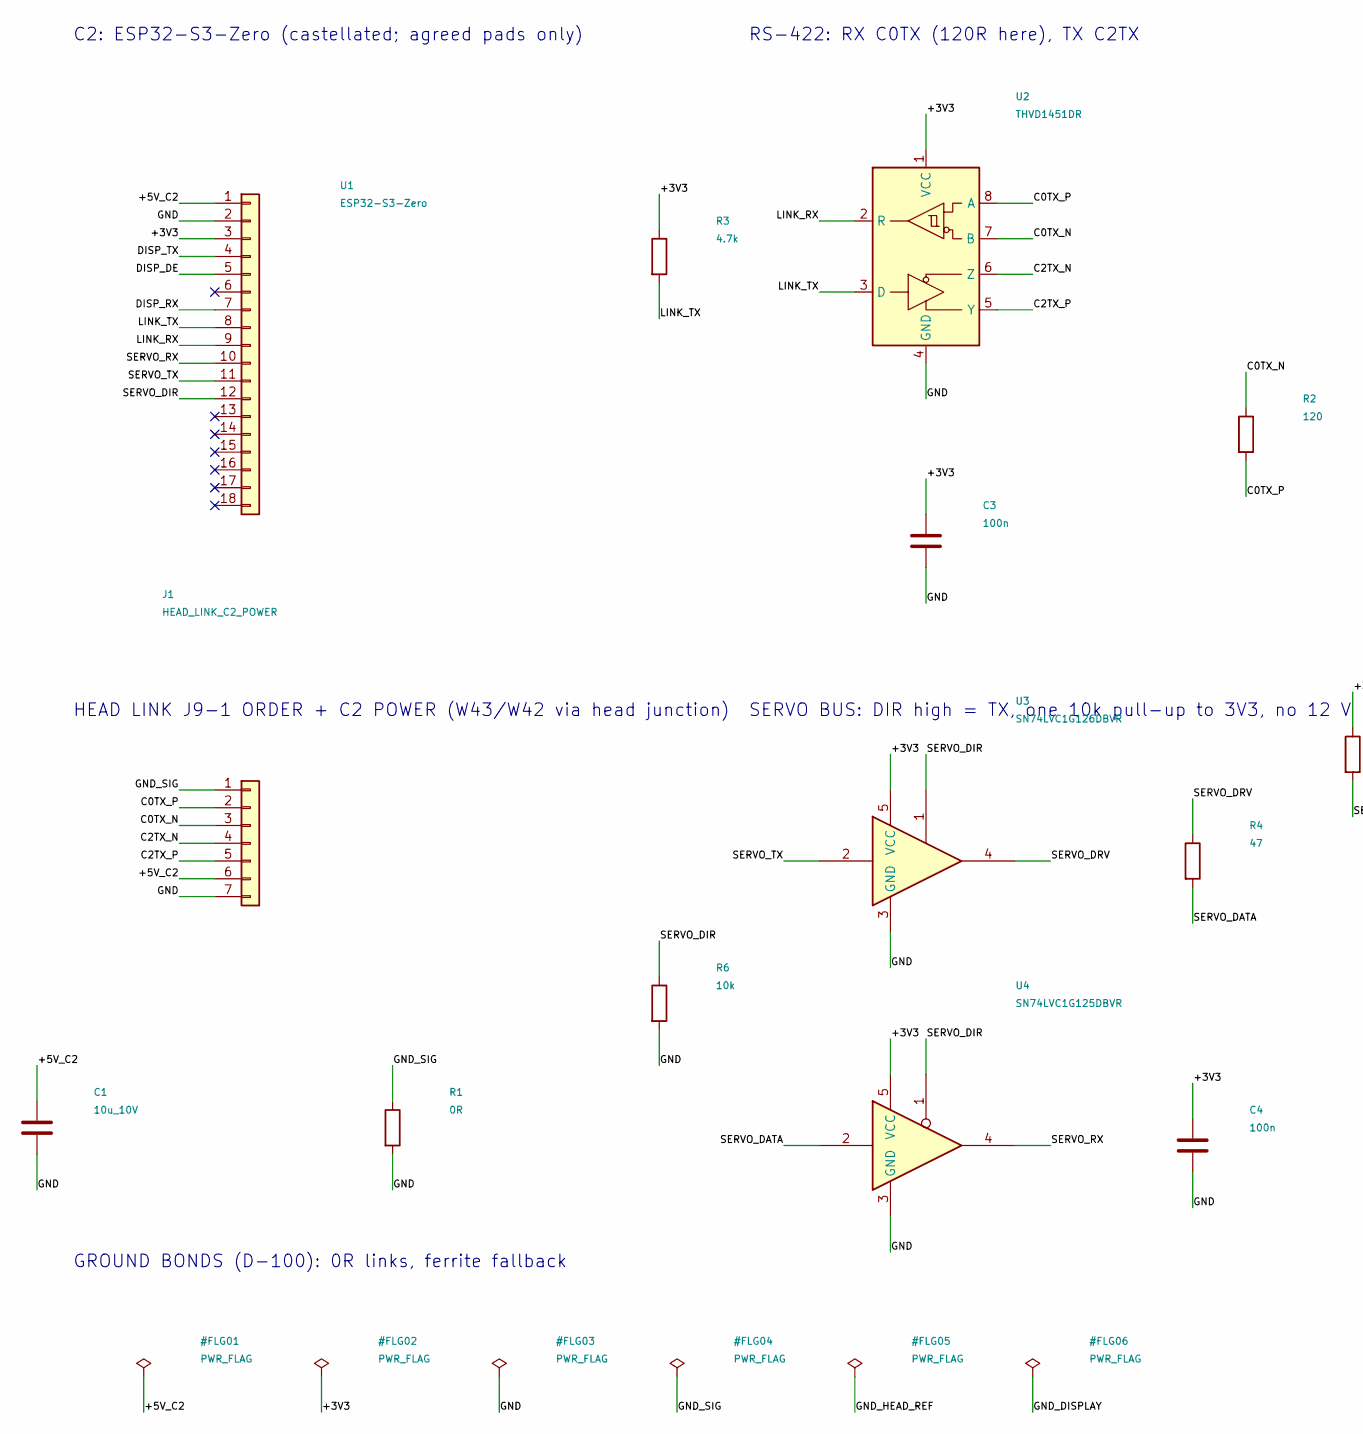
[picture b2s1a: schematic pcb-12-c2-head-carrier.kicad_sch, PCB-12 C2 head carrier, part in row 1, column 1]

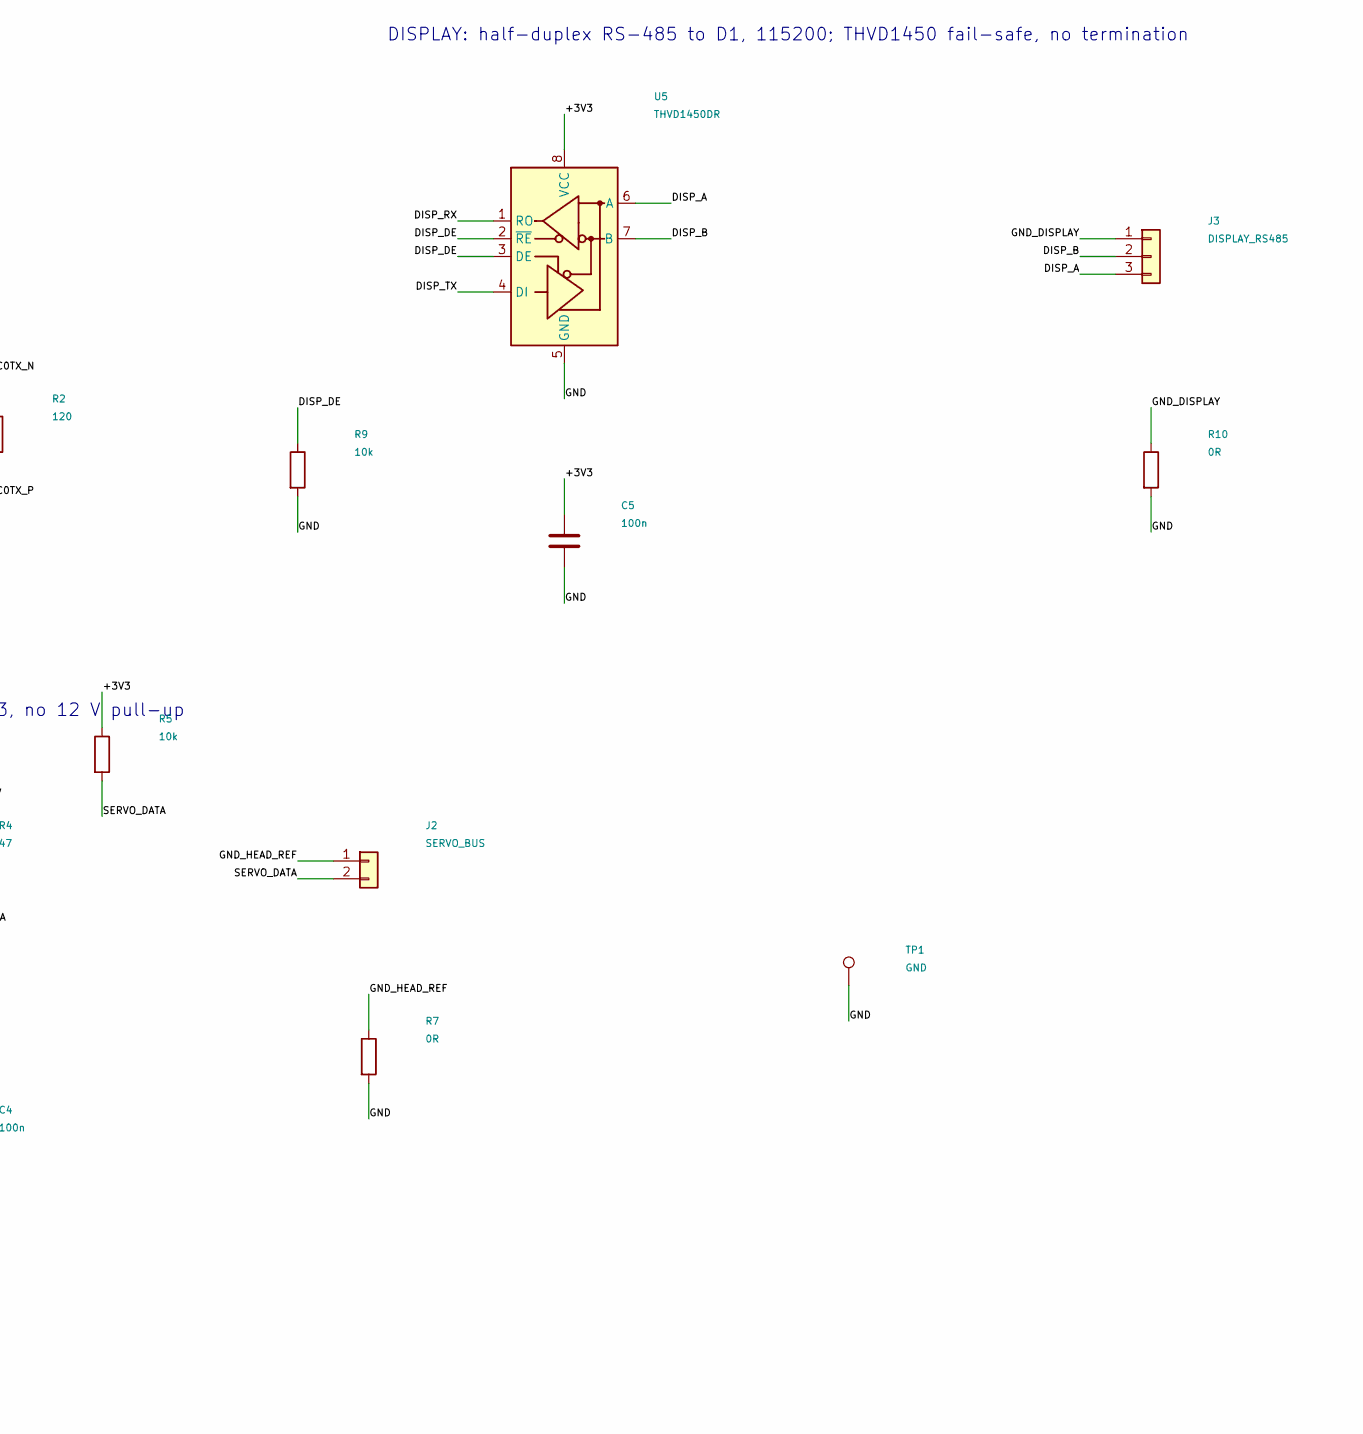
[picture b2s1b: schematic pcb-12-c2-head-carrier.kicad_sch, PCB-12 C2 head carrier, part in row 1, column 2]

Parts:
C1: 10u_10V; C_0805_2012Metric
C3, C4, C5: 100n; C_0603_1608Metric
J1: HEAD_LINK_C2_POWER; JST_GH_BM07B-GHS-TBT_1x07-1MP_P1.25mm_Vertical
J2: SERVO_BUS; JST_GH_BM02B-GHS-TBT_1x02-1MP_P1.25mm_Vertical
J3: DISPLAY_RS485; JST_GH_BM03B-GHS-TBT_1x03-1MP_P1.25mm_Vertical
R1, R7, R10: 0R; R_0603_1608Metric
R2: 120; R_0603_1608Metric
R3: 4.7k; R_0603_1608Metric
R4: 47; R_0603_1608Metric
R5, R6, R9: 10k; R_0603_1608Metric
TP1: GND; TestPoint_Pad_D1.0mm
U1: ESP32-S3-Zero; Waveshare_ESP32-S3-Zero_Castellated
U2: THVD1451DR; SOIC-8_3.9x4.9mm_P1.27mm
U3: SN74LVC1G126DBVR; SOT-23-5
U4: SN74LVC1G125DBVR; SOT-23-5
U5: THVD1450DR; SOIC-8_3.9x4.9mm_P1.27mm

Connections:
/+3V3: C3.1, C4.1, C5.1, R3.1, R5.1, U1.3, U2.1, U3.5, U4.5, U5.8
/+5V_C2: C1.1, J1.6, U1.1
/C0TX_N: J1.3, R2.1, U2.7
/C0TX_P: J1.2, R2.2, U2.8
/C2TX_N: J1.4, U2.6
/C2TX_P: J1.5, U2.5
/DISP_A: J3.3, U5.6
/DISP_B: J3.2, U5.7
/DISP_DE: R9.1, U1.5, U5.2, U5.3
/DISP_RX: U1.7, U5.1
/DISP_TX: U1.4, U5.4
/GND: C1.2, C3.2, C4.2, C5.2, J1.7, R1.2, R6.2, R7.2, R9.2, R10.2, TP1.1 (Pin_1_1), U1.2, U2.4, U3.3, U4.3, U5.5
/GND_DISPLAY: J3.1, R10.1
/GND_HEAD_REF: J2.1, R7.1
/GND_SIG: J1.1, R1.1
/LINK_RX: U1.9, U2.2
/LINK_TX: R3.2, U1.8, U2.3
/SERVO_DATA: J2.2, R4.2, R5.2, U4.2
/SERVO_DIR: R6.1, U1.12, U3.1, U4.1
/SERVO_DRV: R4.1, U3.4
/SERVO_RX: U1.10, U4.4
/SERVO_TX: U1.11, U3.2

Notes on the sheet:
C2: ESP32-S3-Zero (castellated; agreed pads only)
HEAD LINK J9-1 ORDER + C2 POWER (W43/W42 via head junction)
RS-422: RX C0TX (120R here), TX C2TX
SERVO BUS: DIR high = TX, one 10k pull-up to 3V3, no 12 V pull-up
DISPLAY: half-duplex RS-485 to D1, 115200; THVD1450 fail-safe, no termination
GROUND BONDS (D-100): 0R links, ferrite fallback

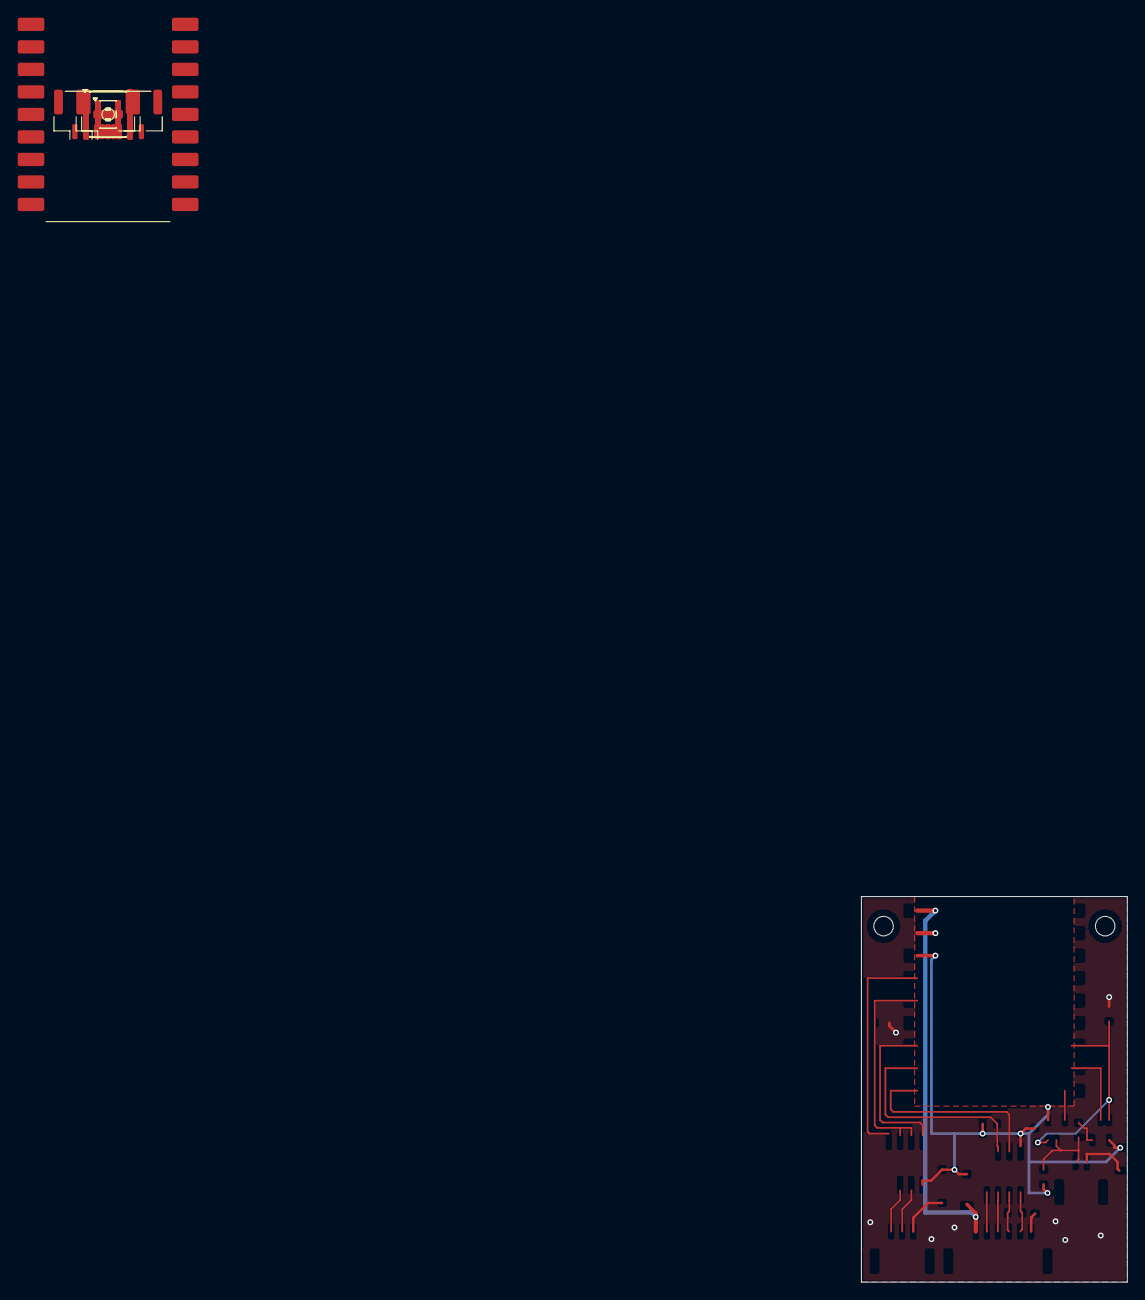
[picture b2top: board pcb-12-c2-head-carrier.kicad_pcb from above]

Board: 2 copper layers, 30.0 x 43.5 mm, 22 parts (0 on the bottom side), 22 nets.

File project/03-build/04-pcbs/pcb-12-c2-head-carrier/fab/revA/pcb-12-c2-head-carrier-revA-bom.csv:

"Comment","Designator","Footprint","Quantity","MPN","Manufacturer","LCSC Part #"
"10u_10V","C1","Capacitor_SMD:C_0805_2012Metric","1","CL21A106KPFNNNE","Samsung",""
"100n","C3,C4,C5","Capacitor_SMD:C_0603_1608Metric","3","CC0603KRX7R9BB104","Yageo",""
"HEAD_LINK_C2_POWER","J1","Connector_JST:JST_GH_BM07B-GHS-TBT_1x07-1MP_P1.25mm_Vertical","1","BM07B-GHS-TBT(LF)(SN)(N)","JST",""
"SERVO_BUS","J2","Connector_JST:JST_GH_BM02B-GHS-TBT_1x02-1MP_P1.25mm_Vertical","1","BM02B-GHS-TBT(LF)(SN)(N)","JST",""
"DISPLAY_RS485","J3","Connector_JST:JST_GH_BM03B-GHS-TBT_1x03-1MP_P1.25mm_Vertical","1","BM03B-GHS-TBT(LF)(SN)(N)","JST",""
"0R","R1,R7,R10","Resistor_SMD:R_0603_1608Metric","3","RC0603JR-070RL","Yageo",""
"120","R2","Resistor_SMD:R_0603_1608Metric","1","RC0603FR-07120RL","Yageo",""
"4.7k","R3","Resistor_SMD:R_0603_1608Metric","1","RC0603FR-074K7L","Yageo",""
"47","R4","Resistor_SMD:R_0603_1608Metric","1","RC0603FR-0747RL","Yageo",""
"10k","R5,R6,R9","Resistor_SMD:R_0603_1608Metric","3","RC0603FR-0710KL","Yageo",""
"ESP32-S3-Zero","U1","pcb12:Waveshare_ESP32-S3-Zero_Castellated","1","ESP32-S3-Zero (SKU 25081, without header)","Waveshare",""
"THVD1451DR","U2","Package_SO:SOIC-8_3.9x4.9mm_P1.27mm","1","THVD1451DR","TI",""
"SN74LVC1G126DBVR","U3","Package_TO_SOT_SMD:SOT-23-5","1","SN74LVC1G126DBVR","TI",""
"SN74LVC1G125DBVR","U4","Package_TO_SOT_SMD:SOT-23-5","1","SN74LVC1G125DBVR","TI",""
"THVD1450DR","U5","Package_SO:SOIC-8_3.9x4.9mm_P1.27mm","1","THVD1450DR","TI",""
